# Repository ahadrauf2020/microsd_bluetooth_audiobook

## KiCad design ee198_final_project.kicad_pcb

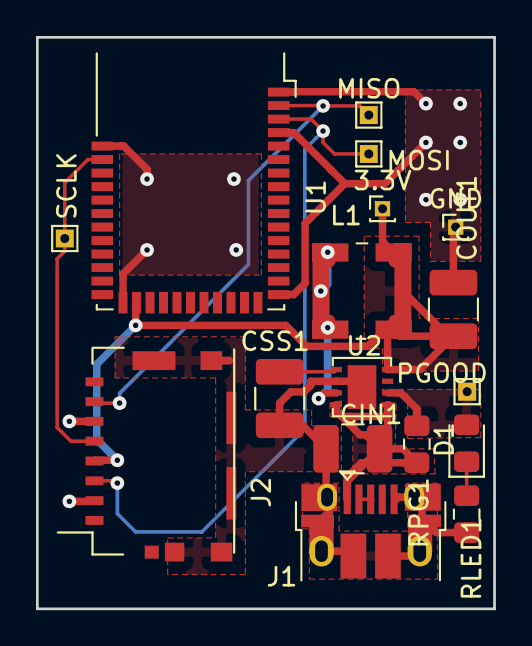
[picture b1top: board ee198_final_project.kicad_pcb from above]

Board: 2 copper layers, 25.4 x 31.8 mm, 17 parts (0 on the bottom side), 11 nets.

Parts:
3.3V: Conn_01x01_Male; PinHeader_1x01_P1.00mm_Vertical
CIN1: 10u; R_1210_3225Metric_Pad1.42x2.65mm_HandSolder
COUT1: 10u; R_1210_3225Metric_Pad1.42x2.65mm_HandSolder
CSS1: 10u; R_1210_3225Metric_Pad1.42x2.65mm_HandSolder
D1: LED; LED_0805_2012Metric_Pad1.15x1.40mm_HandSolder
GND: Conn_01x01_Male; PinHeader_1x01_P1.00mm_Vertical
J1: USB_B_Micro; USB_Micro-B_Amphenol_10103594-0001LF_Horizontal
J2: Micro_SD_Card_Det; Molex_08-1051620001
L1: 100u; L_Wuerth_WE-TPC-1919
MISO: TestPoint; TestPoint_THTPad_1.0x1.0mm_Drill0.5mm
MOSI: TestPoint; TestPoint_THTPad_1.0x1.0mm_Drill0.5mm
PGOOD: TestPoint; TestPoint_THTPad_1.0x1.0mm_Drill0.5mm
RLED1: 1k; R_0805_2012Metric_Pad1.15x1.40mm_HandSolder
RPG1: 1k; R_0805_2012Metric_Pad1.15x1.40mm_HandSolder
SCLK: TestPoint; TestPoint_THTPad_1.0x1.0mm_Drill0.5mm
U1: BL652; Laird_BL651
U2: ADP2302ARDZ-3.3; Analog_LFCSP-8-1EP_3x3mm_P0.5mm_EP1.53x1.85mm

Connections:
/3.3V: 3.3V.1, COUT1.1, J2.4, L1.2, U1.26, U2.4
/5V: CIN1.1, J1.1, RPG1.1, U2.1, U2.8
/MISO: J2.7, MISO.1, U1.2
/MOSI: J2.3, MOSI.1, U1.3
/PGOOD: D1.2, PGOOD.1, RPG1.2, U2.2
/SCLK: J2.5, SCLK.1, U1.38
/SS: CSS1.1, U2.5
/SW: L1.1, U2.7
GND: CIN1.2, COUT1.2, CSS1.2, GND.1, J1.5, J1.6, J2.2, J2.6, J2.10, RLED1.2, U1.1, U1.4, U1.16, U1.27, U1.39, U2.6, U2.9
unnamed: D1.1, RLED1.1
unnamed: J1.2, J1.3

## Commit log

2019-03-30 saving to github
2019-04-08 final changes
